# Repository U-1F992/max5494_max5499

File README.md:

# MAX5494/MAX5495/MAX5496/MAX5497/MAX5498/MAX5499

- https://www.analog.com/products/max5494.html
- https://www.analog.com/products/max5495.html
- https://www.analog.com/products/max5496.html
- https://www.analog.com/products/max5497.html
- https://www.analog.com/products/max5498.html
- https://www.analog.com/products/max5499.html

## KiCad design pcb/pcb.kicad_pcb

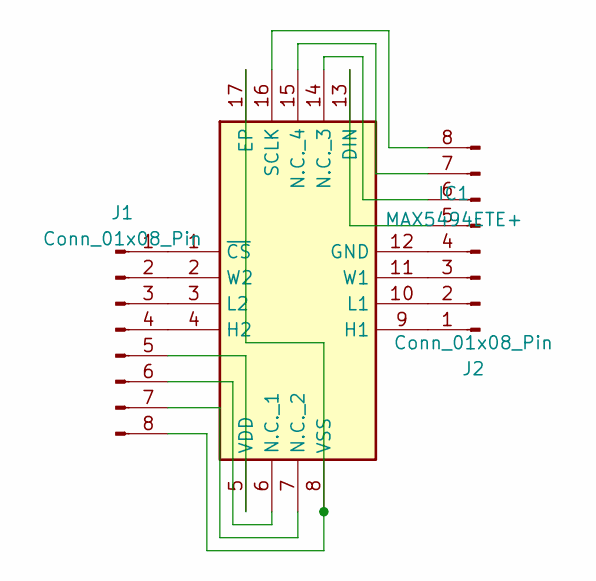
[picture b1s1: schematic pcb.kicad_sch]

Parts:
IC1: MAX5494ETE+; QFN80P500X500X80-17N; Manufacturer_Part_Number MAX5494ETE+; Mouser Part Number 700-MAX5494ETE
J1, J2: Conn_01x08_Pin; PinHeader_1x08_P2.54mm_Vertical

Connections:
unnamed: IC1.13 (DIN), J2.5
unnamed: IC1.8 (VSS), IC1.17 (EP), J1.8
unnamed: IC1.12 (GND), J2.4
unnamed: IC1.9 (H1), J2.1
unnamed: IC1.4 (H2), J1.4
unnamed: IC1.10 (L1), J2.2
unnamed: IC1.3 (L2), J1.3
unnamed: IC1.6 (N.C._1), J1.6
unnamed: IC1.7 (N.C._2), J1.7
unnamed: IC1.14 (N.C._3), J2.6
unnamed: IC1.15 (N.C._4), J2.7
unnamed: IC1.16 (SCLK), J2.8
unnamed: IC1.5 (VDD), J1.5
unnamed: IC1.11 (W1), J2.3
unnamed: IC1.2 (W2), J1.2
unnamed: IC1.1 (~CS), J1.1

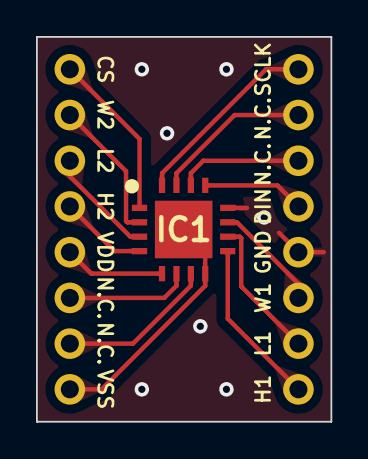
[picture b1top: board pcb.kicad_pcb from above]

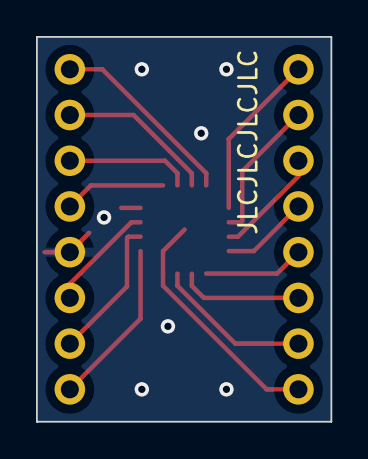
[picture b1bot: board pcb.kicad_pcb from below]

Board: 2 copper layers, 16.4 x 21.4 mm, 3 parts (2 on the bottom side), 16 nets.

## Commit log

2024-01-23 Create LICENSE
2024-01-24 Add test cases
2024-01-24 Remove unused include
2024-02-23 Refactor test
2024-02-23 Add wrapper for ArduinoFramework
2024-02-23 Remove src
2024-02-23 Add breakout board
2024-02-23 Revert "Remove src"
    This reverts commit c1edf2089f053363e2be1cad19987cb997289de0.
2024-02-23 Blink if successful
2024-02-23 Add schematic diagram for testing
2024-03-05 Rename arduino to Arduino
2024-03-09 Remove test/arduino/
